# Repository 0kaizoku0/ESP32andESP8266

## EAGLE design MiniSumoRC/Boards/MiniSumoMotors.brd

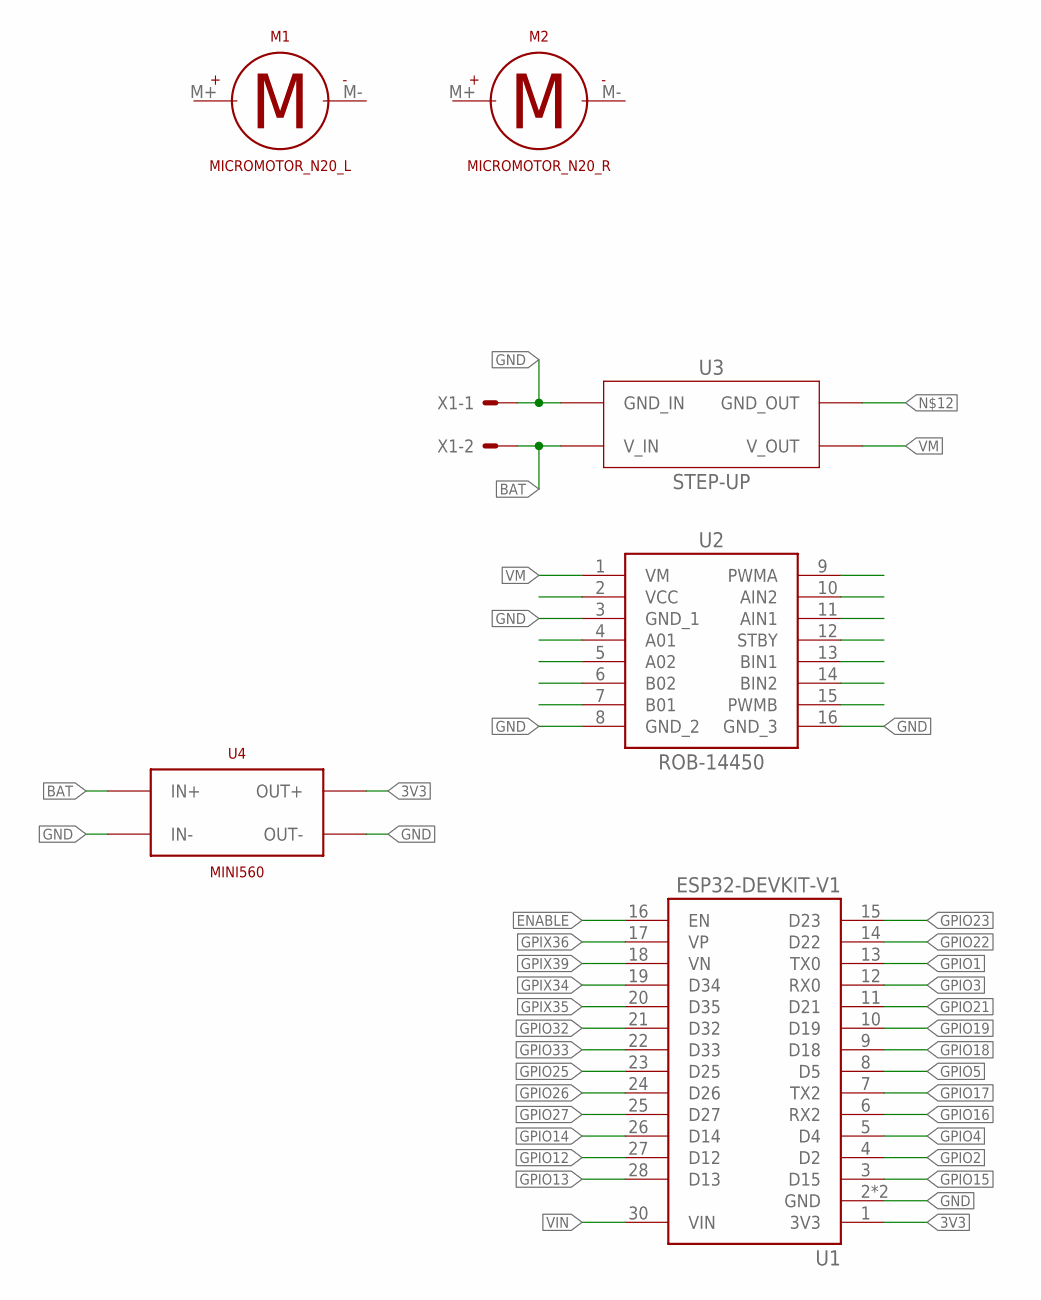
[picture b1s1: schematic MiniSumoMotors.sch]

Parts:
M1: MICROMOTOR_N20_L; MICROMOTOR-L
M2: MICROMOTOR_N20_R; MICROMOTOR-R
U1: ESP32-DEVKIT-V1; MODULE_ESP32_DEVKIT_V1
U2: ROB-14450; ROB14450
U3: STEP-UP
U4: MINI560
X1: 22-23-2021

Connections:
3V3: U1.1 (3V3), U4.P$11 (OUT+), U4.P$12 (OUT+), U4.P$15 (OUT+), U4.P$16 (OUT+)
BAT: U3.V_IN, U4.P$3 (IN+), U4.P$4 (IN+), U4.P$7 (IN+), U4.P$8 (IN+), X1.2
ENABLE: U1.16 (EN)
GND: U1.2 (GND), U1.29 (GND), U2.3 (GND_1), U2.8 (GND_2), U2.16 (GND_3), U3.GND_IN, U4.P$1 (IN-), U4.P$2 (IN-), U4.P$5 (IN-), U4.P$6 (IN-), U4.P$9 (OUT-), U4.P$10 (OUT-), U4.P$13 (OUT-), U4.P$14 (OUT-), X1.1
GPIO1: U1.13 (TX0)
GPIO2: U1.4 (D2)
GPIO3: U1.12 (RX0)
GPIO4: U1.5 (D4)
GPIO5: U1.8 (D5)
GPIO12: U1.27 (D12)
GPIO13: U1.28 (D13)
GPIO14: U1.26 (D14)
GPIO15: U1.3 (D15)
GPIO16: U1.6 (RX2)
GPIO17: U1.7 (TX2)
GPIO18: U1.9 (D18)
GPIO19: U1.10 (D19)
GPIO21: U1.11 (D21)
GPIO22: U1.14 (D22)
GPIO23: U1.15 (D23)
GPIO25: U1.23 (D25)
GPIO26: U1.24 (D26)
GPIO27: U1.25 (D27)
GPIO32: U1.21 (D32)
GPIO33: U1.22 (D33)
GPIX34: U1.19 (D34)
GPIX35: U1.20 (D35)
GPIX36: U1.17 (VP)
GPIX39: U1.18 (VN)
VIN: U1.30 (VIN)
VM: U2.1 (VM), U3.V_OUT

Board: 2 copper layers, 7 parts (4 on the bottom side), 4 nets, no tracks yet.

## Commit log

2023-03-27 01_Blink
2023-04-10 Update Files
2023-04-10 Deleted drivers folder
2023-04-10 Deleted temp files
2023-04-16 Updated Schematic
2023-04-17 Board
2023-05-01 Move PCBs to another repo
